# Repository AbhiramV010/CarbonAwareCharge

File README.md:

Carbon Aware Charging logic used in \Iris-Lite

See README.md for the repository https://github.com/AbhiramV010/Iris-Lite for more details and the other code that goes with it

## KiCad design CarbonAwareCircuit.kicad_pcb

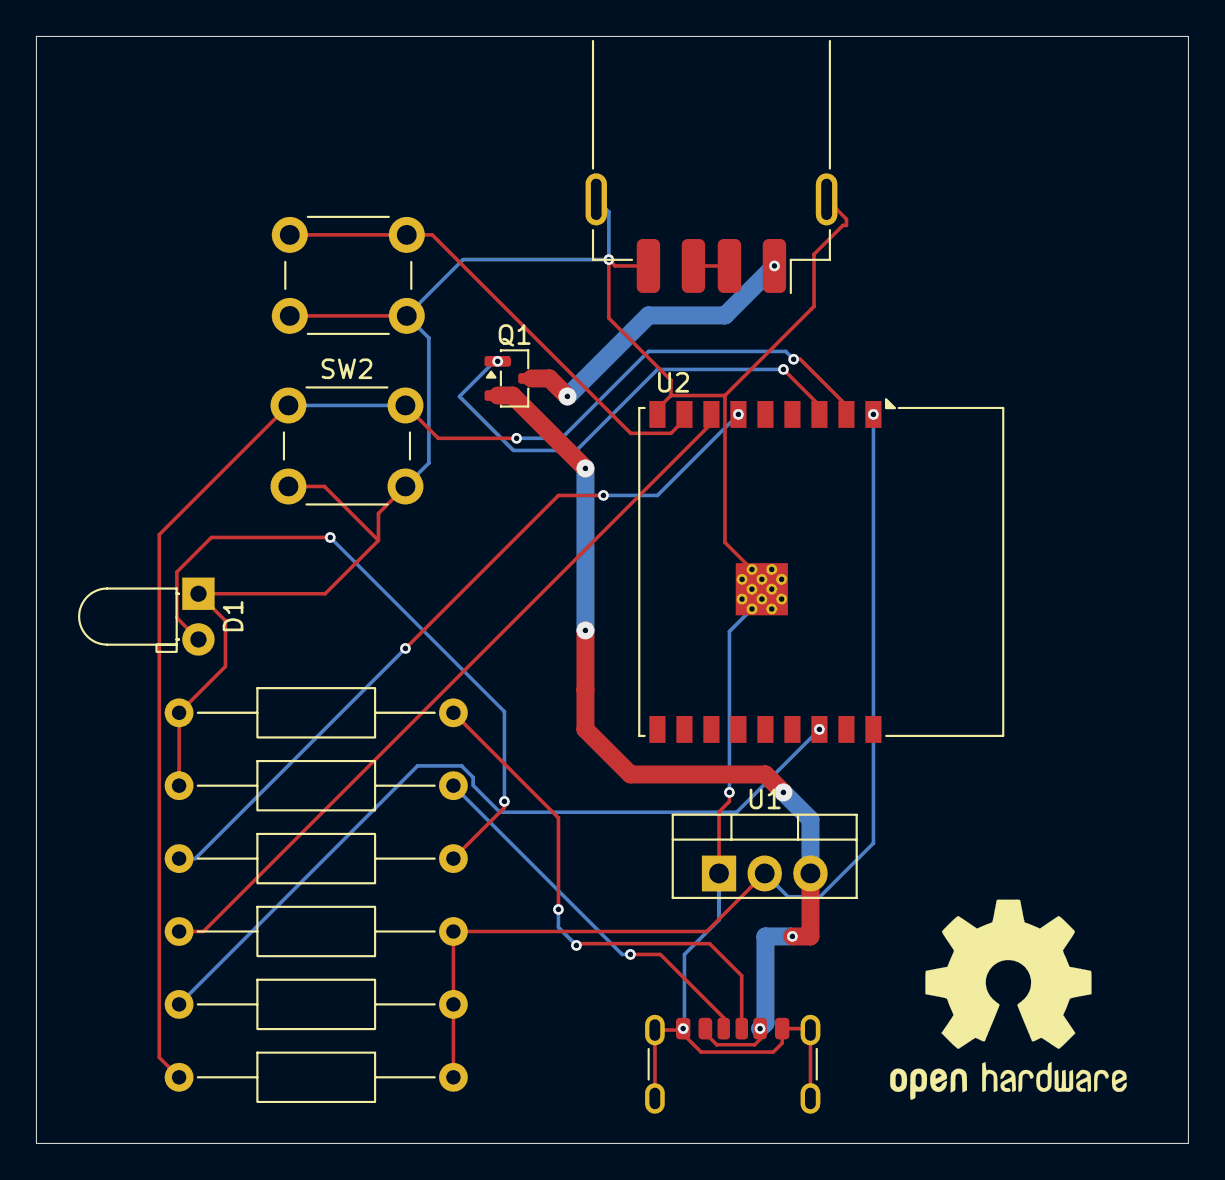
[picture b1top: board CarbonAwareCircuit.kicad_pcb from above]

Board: 2 copper layers, 64.0 x 61.5 mm, 14 parts (0 on the bottom side), 14 nets.

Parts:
D1: LED; LED_D3.0mm_Horizontal_O1.27mm_Z2.0mm_Clear
J1: USB_C_Receptacle_USB2.0_14P; USB_C_Receptacle_GCT_USB4125-xx-x_6P_TopMnt_Horizontal
J2: USB_A; USB_A_Receptacle_GCT_USB1046
Q1: AO3401A; SOT-23
R1, R2: 5.1kΩ; R_Axial_DIN0207_L6.3mm_D2.5mm_P15.24mm_Horizontal
R3: 330Ω; R_Axial_DIN0207_L6.3mm_D2.5mm_P15.24mm_Horizontal
R4, R5, R6: 10kΩ; R_Axial_DIN0207_L6.3mm_D2.5mm_P15.24mm_Horizontal
SW1: SW_Push; SW_PUSH_6mm_H4.3mm
SW2: SW_Push; SW_PUSH_6mm_H7.3mm
U1: LD1117V; TO-220-3_Vertical
U2: ESP32-C3-WROOM-02

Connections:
unnamed: D1.2 (A), R3.2
unnamed: D1.1 (K), J1.A12 (GND), J1.B12 (GND), J1.SH (SHIELD), J2.4 (GND), J2.SH (Shield), R1.1, R2.1, SW1.2, SW2.2, U1.1 (GND), U2.9 (GND), U2.19 (GND)
unnamed: J1.A5 (CC1), R2.2
unnamed: J1.B5 (CC2), R1.2
unnamed: J2.2 (D-), J2.3 (D+)
unnamed: J2.1 (VBUS), Q1.3 (D)
unnamed: Q1.1 (G), U2.3 (IO4)
unnamed: J1.A9 (VBUS), J1.B9 (VBUS), Q1.2 (S), U1.3 (VI)
unnamed: R4.2, R5.2, R6.2, U1.2 (VO), U2.1 (3V3)
unnamed: R6.1, SW2.1, U2.2 (EN)
unnamed: R5.1, U2.16 (IO2)
unnamed: R3.1, U2.6 (IO7)
unnamed: R4.1, U2.7 (IO8)
unnamed: SW1.1, U2.8 (IO9)

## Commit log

2026-04-03 initial commit, first files
2026-04-03 Update .gitignore for ESP-IDF and KiCad files
2026-04-06 Add GNU General Public License version 2
2026-04-08 Add filters for KiCad project and schematic files
2026-04-08 Added the C3 and Linear Voltage Regulator
2026-04-09 added Error LED
2026-04-09 Wired pull up resistors & boot/reset buttons
2026-04-11 connected input port & ERR_LED
2026-04-12 defined passVCC
2026-04-12 eeschema done
2026-04-12 massive strides in pcbnew
2026-04-13 added silkscreen
2026-04-15 changed output to female
2026-04-17 not a clue what has been done...
2026-05-02 added eeschema, pcbnew, and 3d render
2026-05-06 Enhance README with additional details about repository
    Expanded the description of the repository link.
2026-05-08 added stls
